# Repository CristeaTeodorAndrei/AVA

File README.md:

# AVA

AVA - Flight Computer

AVA is the rocket's main flight computer.

This is the second iteration of the flight computer

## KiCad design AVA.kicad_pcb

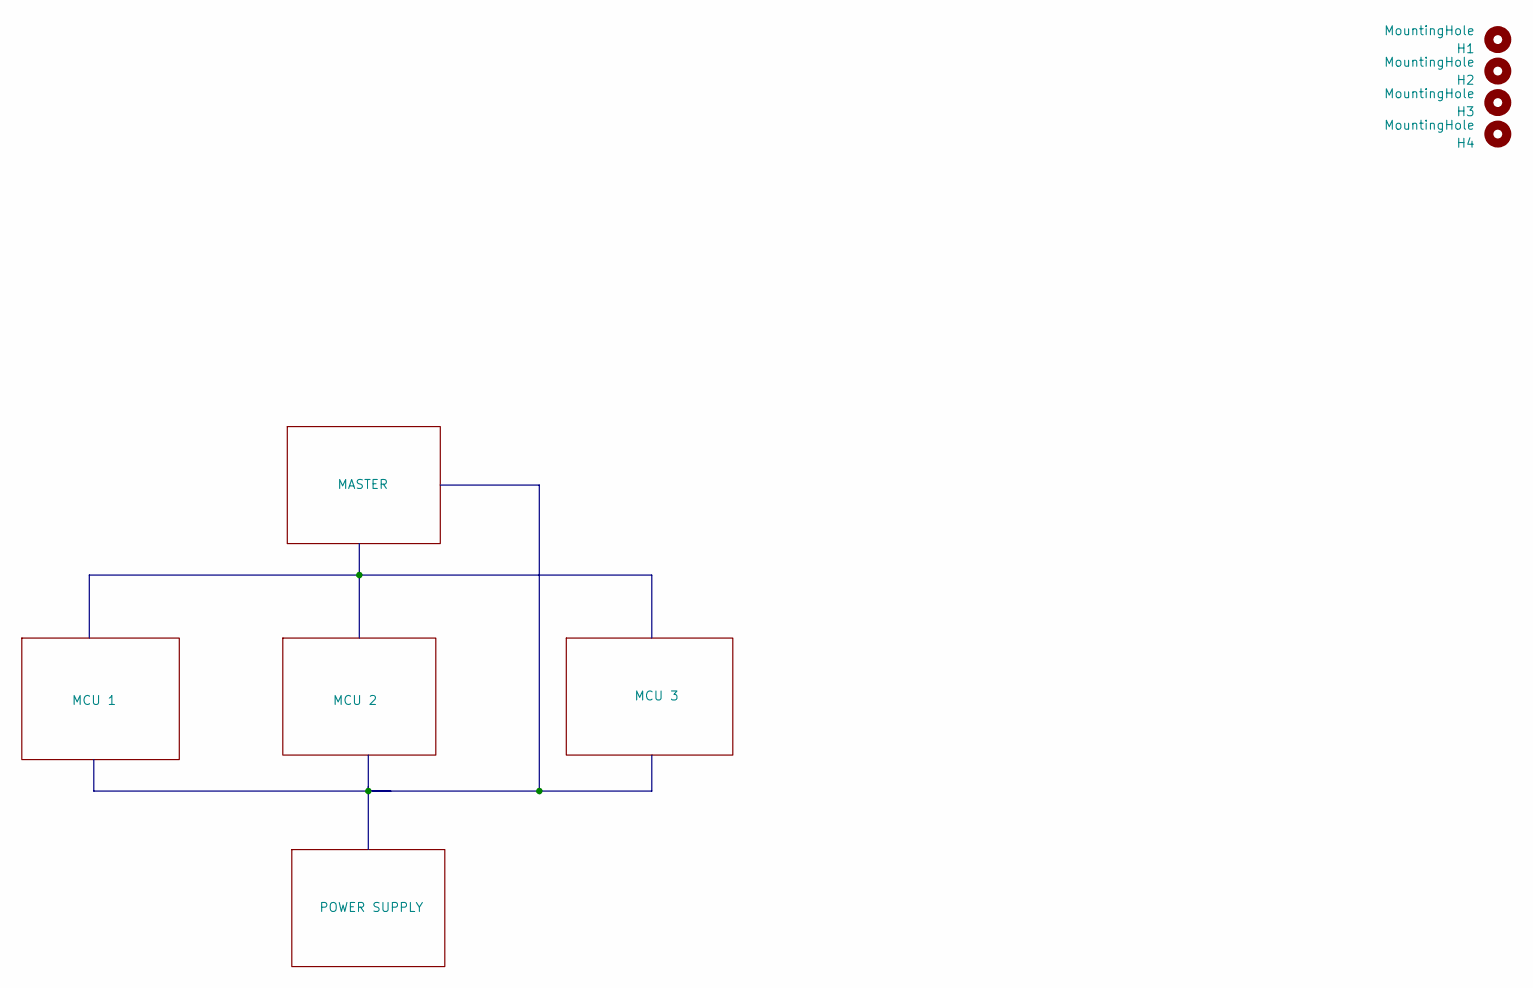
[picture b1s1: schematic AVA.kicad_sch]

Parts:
H1, H2, H3, H4: MountingHole; MountingHole_3.5mm

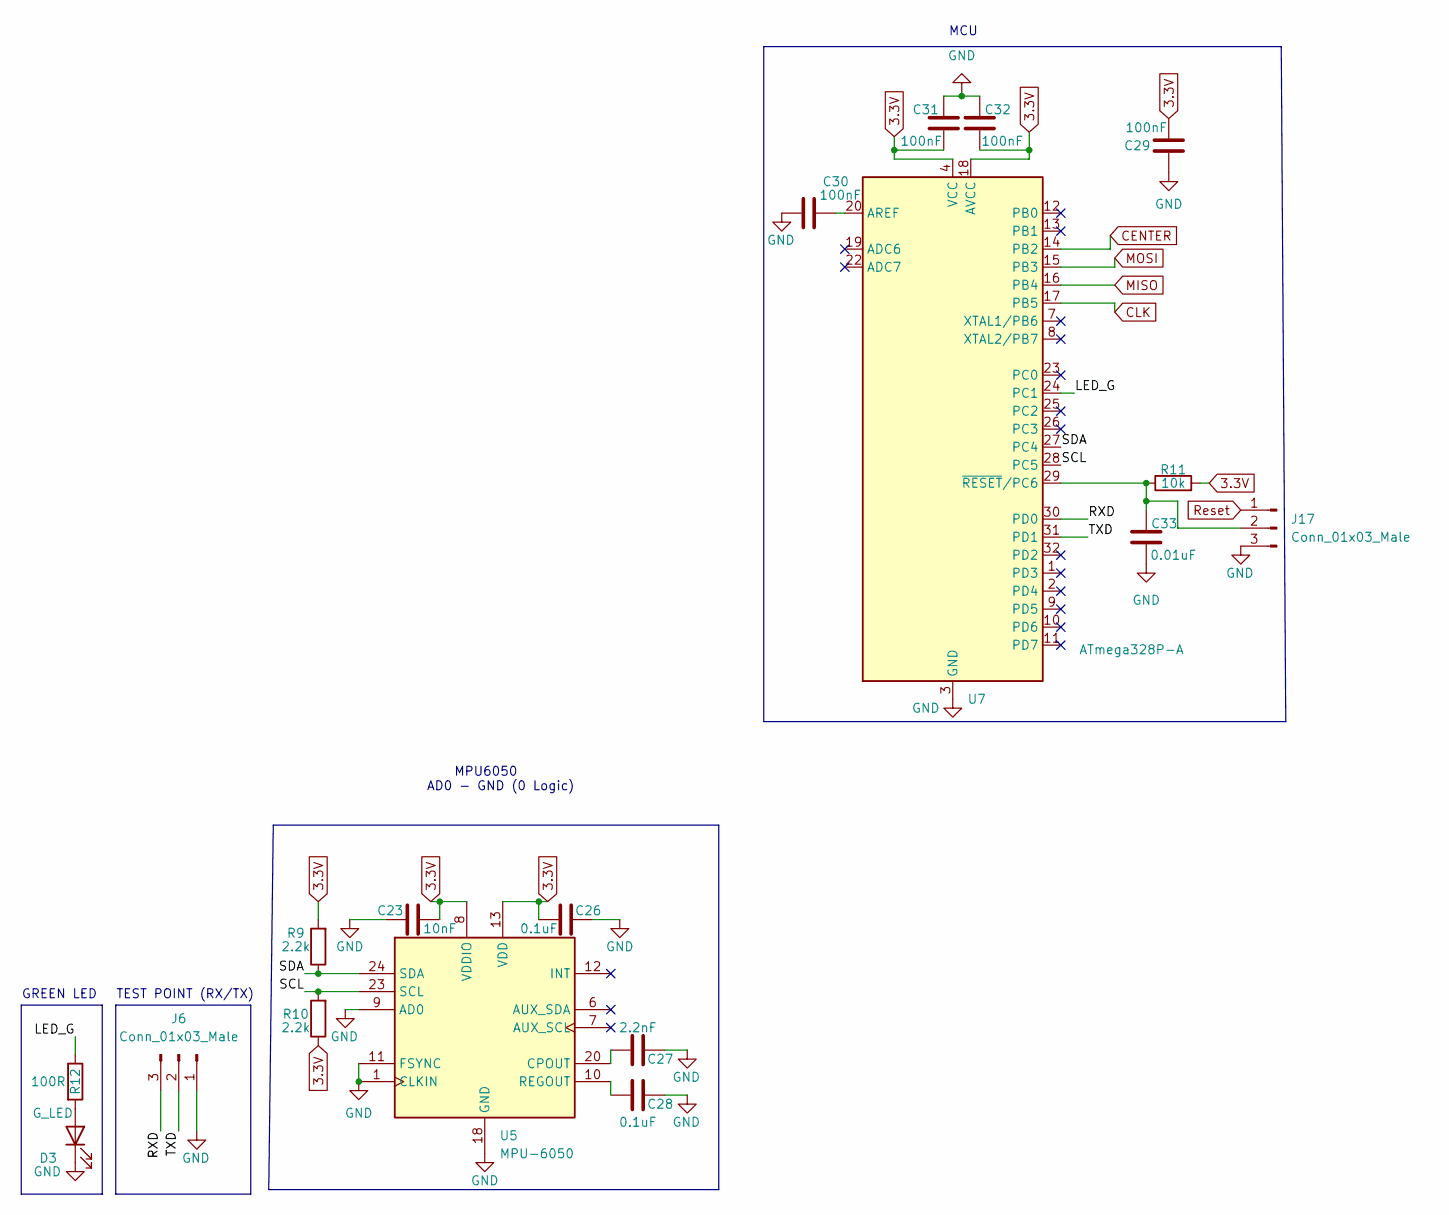
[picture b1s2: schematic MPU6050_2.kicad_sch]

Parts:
C23: 10nF; C_0603_1608Metric
C26, C28: 0.1uF; C_0603_1608Metric
C27: 2.2nF; C_0603_1608Metric
C29, C30, C31, C32: 100nF; C_0603_1608Metric
C33: 0.01uF; C_0603_1608Metric
D3: G_LED; LED_0603_1608Metric
J6, J17: Conn_01x03_Male; PinHeader_1x03_P2.54mm_Vertical
R9, R10: 2.2k; R_0603_1608Metric
R11: 10k; R_0603_1608Metric
R12: 100R; R_0603_1608Metric
U5: MPU-6050; InvenSense_QFN-24_4x4mm_P0.5mm
U7: ATmega328P-A; TQFP-32_7x7mm_P0.8mm

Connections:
3.3V: C23.2, C26.1, C29.1, C31.1, C32.1, R9.2, R10.1, R11.2, U5.8 (VDDIO), U5.13 (VDD), U7.4 (VCC), U7.6 (VCC), U7.18 (AVCC); also elsewhere on the board
/MCU 2/LED_G: R12.1, U7.24 (PC1)
/MCU 2/RXD: J6.3, U7.30 (PD0)
/MCU 2/SCL: R10.2, U5.23 (SCL), U7.28 (PC5)
/MCU 2/SDA: R9.1, U5.24 (SDA), U7.27 (PC4)
/MCU 2/TXD: J6.2, U7.31 (PD1)
CENTER: U7.14 (PB2); also elsewhere on the board
CLK: U7.17 (PB5); also elsewhere on the board
GND: C23.1, C26.2, C27.2, C28.2, C29.2, C30.1, C31.2, C32.2, C33.2, D3.1 (K), J6.1, J17.3, U5.1 (CLKIN), U5.9 (AD0), U5.11 (FSYNC), U5.18 (GND), U7.3 (GND), U7.5 (GND), U7.21 (GND); also elsewhere on the board
MISO: U7.16 (PB4); also elsewhere on the board
MOSI: U7.15 (PB3); also elsewhere on the board
unnamed: C27.1, U5.20 (CPOUT)
unnamed: C28.1, U5.10 (REGOUT)
unnamed: C30.2, U7.20 (AREF)
unnamed: C33.1, J17.2, R11.1, U7.29 (~RESET/PC6)
unnamed: D3.2 (A), R12.2
Reset: J17.1; also elsewhere on the board

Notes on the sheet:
MPU6050 AD0 - GND (0 Logic)
MCU
TEST POINT (RX/TX)
GREEN LED

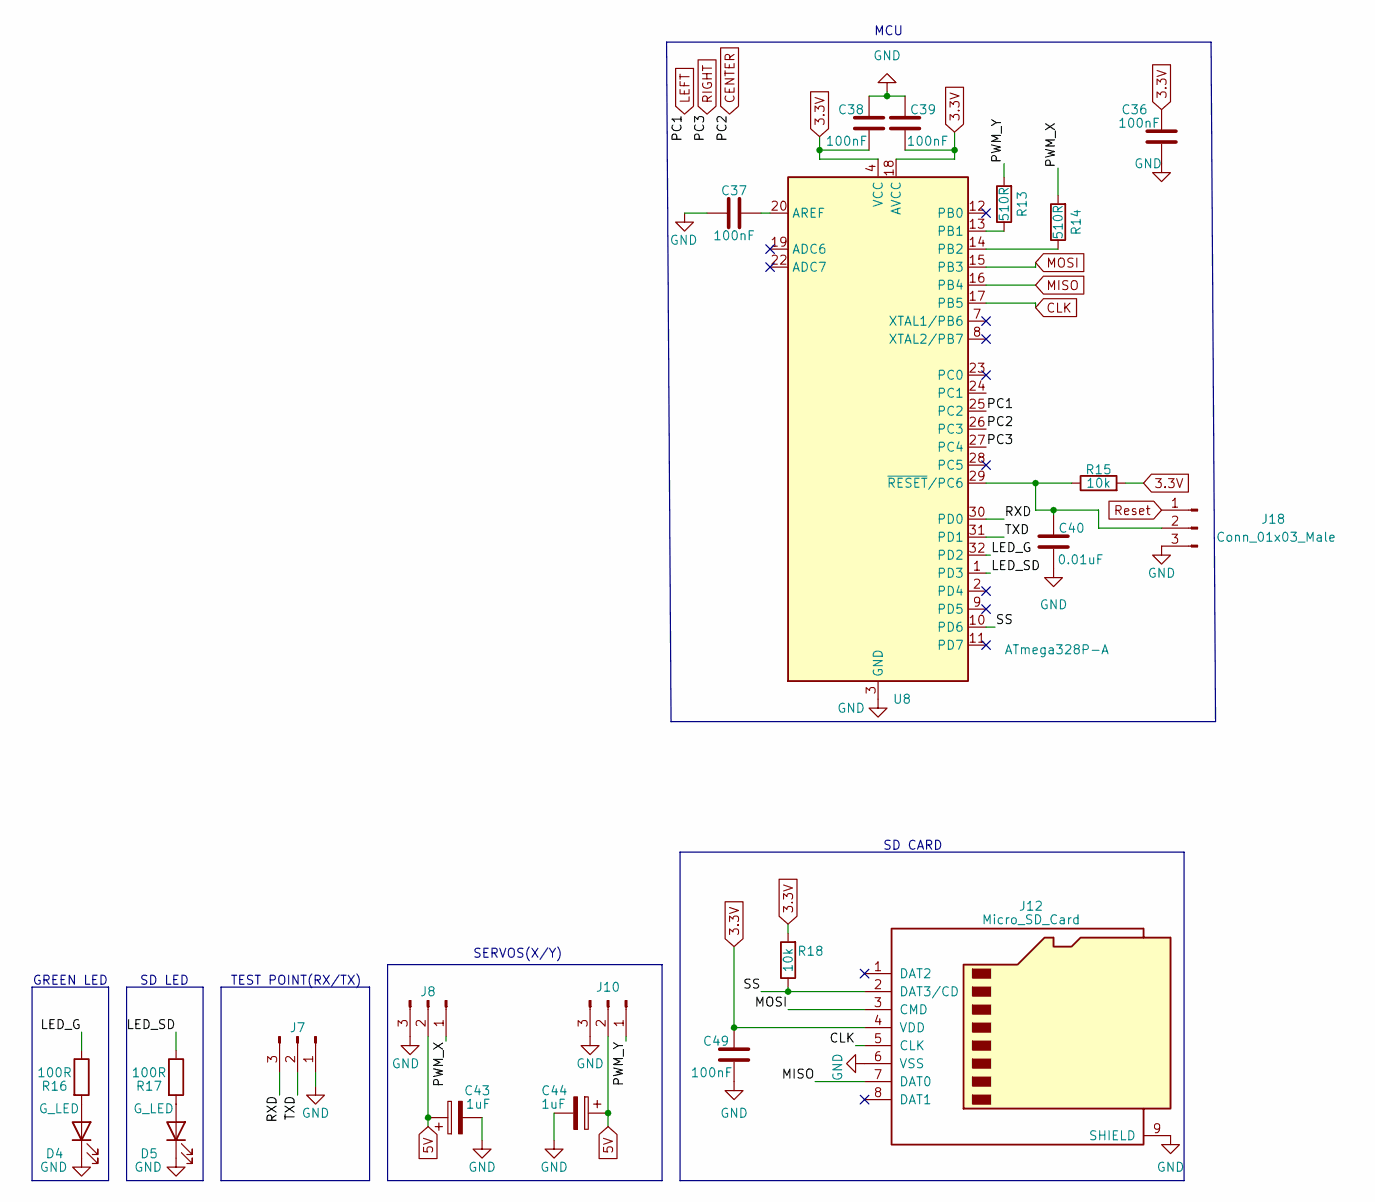
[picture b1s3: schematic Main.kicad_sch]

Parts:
C36, C37, C38, C39, C49: 100nF; C_0603_1608Metric
C40: 0.01uF; C_0603_1608Metric
C43, C44: 1uF; CP_Elec_4x5.4
D4, D5: G_LED; LED_0603_1608Metric
J7, J18: Conn_01x03_Male; PinHeader_1x03_P2.54mm_Vertical
J8: X; PinHeader_1x03_P2.54mm_Vertical
J10: Y; PinHeader_1x03_P2.54mm_Vertical
J12: Micro_SD_Card; microSD_HC_Wuerth_693072010801
R13, R14: 510R; R_0603_1608Metric
R15, R18: 10k; R_0603_1608Metric
R16, R17: 100R; R_0603_1608Metric
U8: ATmega328P-A; TQFP-32_7x7mm_P0.8mm

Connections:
3.3V: C36.1, C38.1, C39.1, C49.2, J12.4 (VDD), R15.2, R18.2, U8.4 (VCC), U8.6 (VCC), U8.18 (AVCC); also elsewhere on the board
5V: C43.1, C44.1, J8.2, J10.2; also elsewhere on the board
/MASTER/LED_G: R16.1, U8.32 (PD2)
/MASTER/LED_SD: R17.1, U8.1 (PD3)
/MASTER/PWM_X: J8.1, R14.2
/MASTER/PWM_Y: J10.1, R13.2
/MASTER/RXD: J7.3, U8.30 (PD0)
/MASTER/SS: J12.2 (DAT3/CD), R18.1, U8.10 (PD6)
/MASTER/TXD: J7.2, U8.31 (PD1)
CENTER: U8.26 (PC3); also elsewhere on the board
CLK: J12.5 (CLK), U8.17 (PB5); also elsewhere on the board
GND: C36.2, C37.1, C38.2, C39.2, C40.2, C43.2, C44.2, C49.1, D4.1 (K), D5.1 (K), J7.1, J8.3, J10.3, J12.6 (VSS), J12.9 (SHIELD), J18.3, U8.3 (GND), U8.5 (GND), U8.21 (GND); also elsewhere on the board
LEFT: U8.25 (PC2); also elsewhere on the board
MISO: J12.7 (DAT0), U8.16 (PB4); also elsewhere on the board
MOSI: J12.3 (CMD), U8.15 (PB3); also elsewhere on the board
unnamed: C37.2, U8.20 (AREF)
unnamed: C40.1, J18.2, R15.1, U8.29 (~RESET/PC6)
unnamed: D4.2 (A), R16.2
unnamed: D5.2 (A), R17.2
unnamed: R13.1, U8.13 (PB1)
unnamed: R14.1, U8.14 (PB2)
RIGHT: U8.27 (PC4); also elsewhere on the board
Reset: J18.1; also elsewhere on the board

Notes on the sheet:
SERVOS(X/Y)
SD LED
MCU
SD CARD
TEST POINT(RX/TX)
GREEN LED

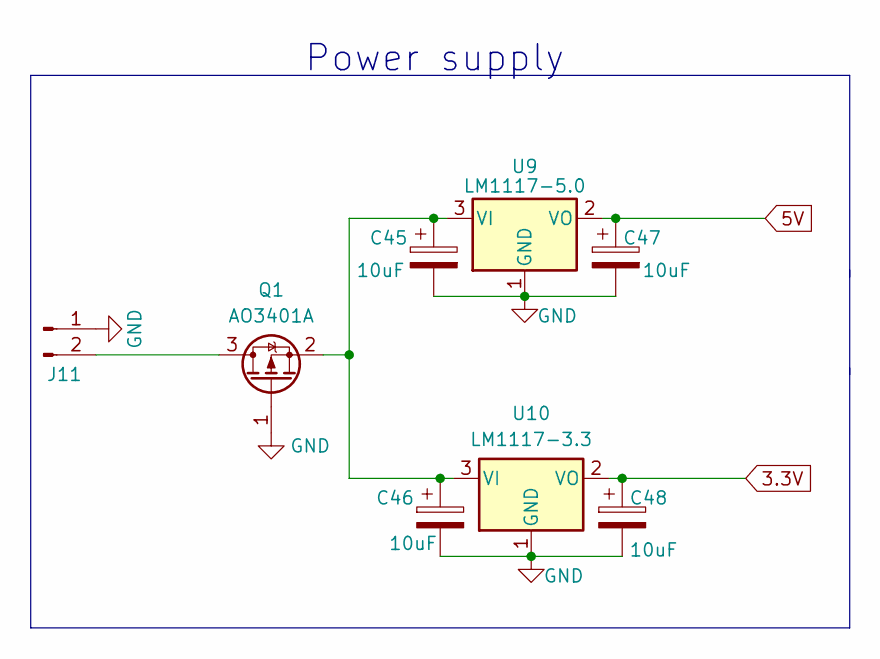
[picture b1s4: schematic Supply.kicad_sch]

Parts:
C45, C46, C47, C48: 10uF; C_1206_3216Metric
J11: Conn_01x02_Male; PinHeader_1x02_P2.54mm_Vertical
Q1: AO3401A; SOT-23
U9: LM1117-5.0; SOT-223-3_TabPin2
U10: LM1117-3.3; SOT-223-3_TabPin2

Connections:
3.3V: C48.1, U10.2 (VO); also elsewhere on the board
5V: C47.1, U9.2 (VO); also elsewhere on the board
GND: C45.2, C46.2, C47.2, C48.2, J11.1, Q1.1 (G), U9.1 (GND), U10.1 (GND); also elsewhere on the board
unnamed: C45.1, C46.1, Q1.2 (S), U9.3 (VI), U10.3 (VI)
unnamed: J11.2, Q1.3 (D)

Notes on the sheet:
Power supply

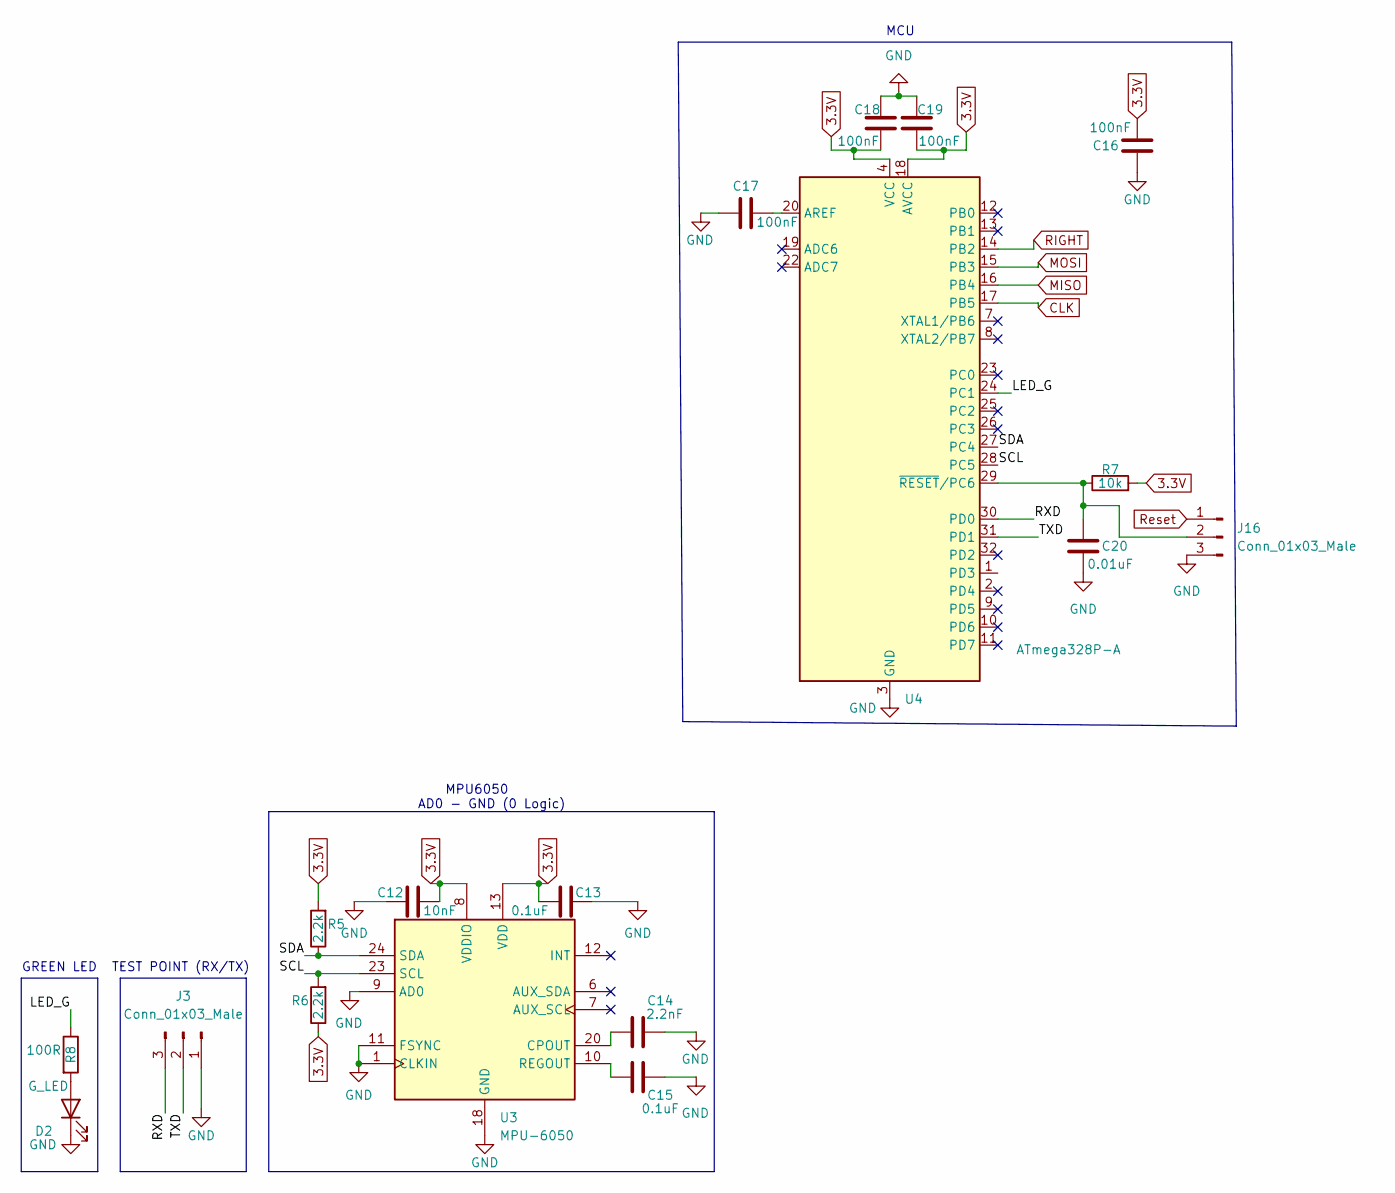
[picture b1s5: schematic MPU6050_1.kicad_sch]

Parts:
C12: 10nF; C_0603_1608Metric
C13, C15: 0.1uF; C_0603_1608Metric
C14: 2.2nF; C_0603_1608Metric
C16, C17, C18, C19: 100nF; C_0603_1608Metric
C20: 0.01uF; C_0603_1608Metric
D2: G_LED; LED_0603_1608Metric
J3, J16: Conn_01x03_Male; PinHeader_1x03_P2.54mm_Vertical
R5, R6: 2.2k; R_0603_1608Metric
R7: 10k; R_0603_1608Metric
R8: 100R; R_0603_1608Metric
U3: MPU-6050; InvenSense_QFN-24_4x4mm_P0.5mm
U4: ATmega328P-A; TQFP-32_7x7mm_P0.8mm

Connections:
3.3V: C12.2, C13.1, C16.1, C18.1, C19.1, R5.2, R6.1, R7.2, U3.8 (VDDIO), U3.13 (VDD), U4.4 (VCC), U4.6 (VCC), U4.18 (AVCC); also elsewhere on the board
/MCU 3/LED_G: R8.1, U4.24 (PC1)
/MCU 3/RXD: J3.3, U4.30 (PD0)
/MCU 3/SCL: R6.2, U3.23 (SCL), U4.28 (PC5)
/MCU 3/SDA: R5.1, U3.24 (SDA), U4.27 (PC4)
/MCU 3/TXD: J3.2, U4.31 (PD1)
CLK: U4.17 (PB5); also elsewhere on the board
GND: C12.1, C13.2, C14.2, C15.2, C16.2, C17.1, C18.2, C19.2, C20.2, D2.1 (K), J3.1, J16.3, U3.1 (CLKIN), U3.9 (AD0), U3.11 (FSYNC), U3.18 (GND), U4.3 (GND), U4.5 (GND), U4.21 (GND); also elsewhere on the board
MISO: U4.16 (PB4); also elsewhere on the board
MOSI: U4.15 (PB3); also elsewhere on the board
unnamed: C14.1, U3.20 (CPOUT)
unnamed: C15.1, U3.10 (REGOUT)
unnamed: C17.2, U4.20 (AREF)
unnamed: C20.1, J16.2, R7.1, U4.29 (~RESET/PC6)
unnamed: D2.2 (A), R8.2
RIGHT: U4.14 (PB2); also elsewhere on the board
Reset: J16.1; also elsewhere on the board

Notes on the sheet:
MPU6050 AD0 - GND (0 Logic)
MCU
GREEN LED
TEST POINT (RX/TX)

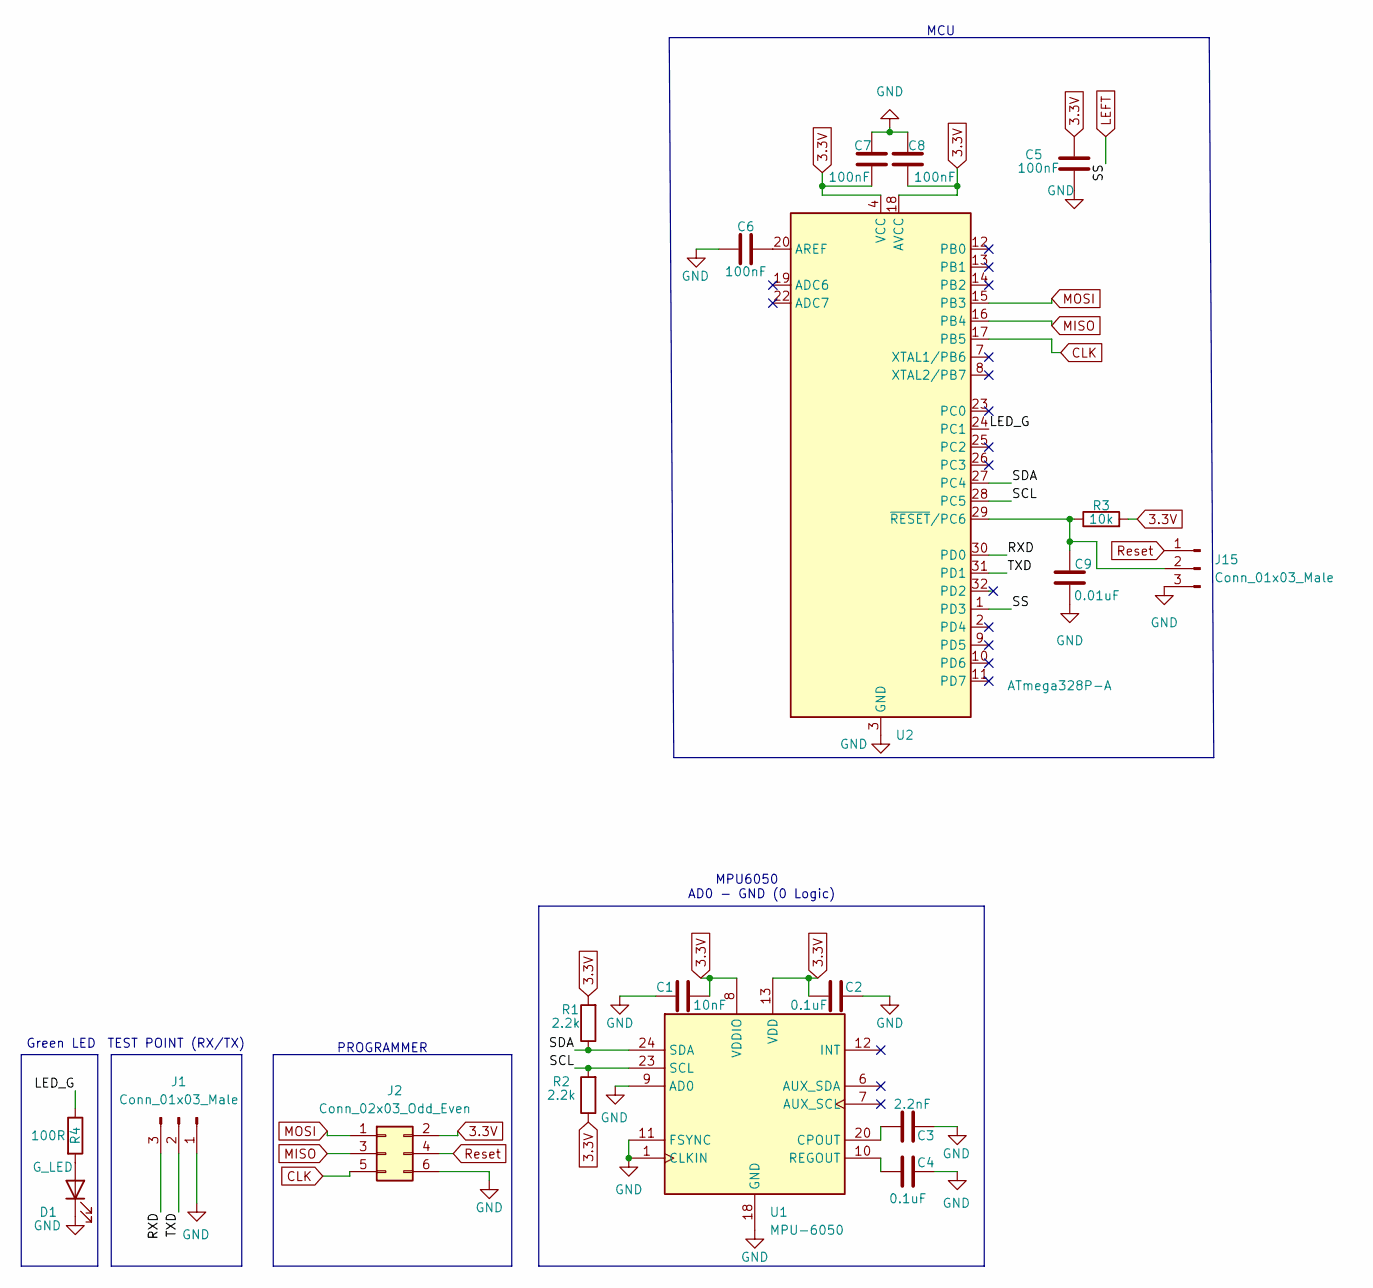
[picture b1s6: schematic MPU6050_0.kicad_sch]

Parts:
C1: 10nF; C_0603_1608Metric
C2, C4: 0.1uF; C_0603_1608Metric
C3: 2.2nF; C_0603_1608Metric
C5, C6, C7, C8: 100nF; C_0603_1608Metric
C9: 0.01uF; C_0603_1608Metric
D1: G_LED; LED_0603_1608Metric
J1, J15: Conn_01x03_Male; PinHeader_1x03_P2.54mm_Vertical
J2: Conn_02x03_Odd_Even; PinHeader_2x03_P2.54mm_Vertical
R1, R2: 2.2k; R_0603_1608Metric
R3: 10k; R_0603_1608Metric
R4: 100R; R_0603_1608Metric
U1: MPU-6050; InvenSense_QFN-24_4x4mm_P0.5mm
U2: ATmega328P-A; TQFP-32_7x7mm_P0.8mm

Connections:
3.3V: C1.2, C2.1, C5.1, C7.1, C8.1, J2.2, R1.2, R2.1, R3.2, U1.8 (VDDIO), U1.13 (VDD), U2.4 (VCC), U2.6 (VCC), U2.18 (AVCC); also elsewhere on the board
/MCU 1/LED_G: R4.1, U2.24 (PC1)
/MCU 1/RXD: J1.3, U2.30 (PD0)
/MCU 1/SCL: R2.2, U1.23 (SCL), U2.28 (PC5)
/MCU 1/SDA: R1.1, U1.24 (SDA), U2.27 (PC4)
/MCU 1/TXD: J1.2, U2.31 (PD1)
CLK: J2.5, U2.17 (PB5); also elsewhere on the board
GND: C1.1, C2.2, C3.2, C4.2, C5.2, C6.1, C7.2, C8.2, C9.2, D1.1 (K), J1.1, J2.6, J15.3, U1.1 (CLKIN), U1.9 (AD0), U1.11 (FSYNC), U1.18 (GND), U2.3 (GND), U2.5 (GND), U2.21 (GND); also elsewhere on the board
LEFT: U2.1 (PD3); also elsewhere on the board
MISO: J2.3, U2.16 (PB4); also elsewhere on the board
MOSI: J2.1, U2.15 (PB3); also elsewhere on the board
unnamed: C3.1, U1.20 (CPOUT)
unnamed: C4.1, U1.10 (REGOUT)
unnamed: C6.2, U2.20 (AREF)
unnamed: C9.1, J15.2, R3.1, U2.29 (~RESET/PC6)
unnamed: D1.2 (A), R4.2
Reset: J2.4, J15.1; also elsewhere on the board

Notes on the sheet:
MPU6050 AD0 - GND (0 Logic)
MCU
TEST POINT (RX/TX)
PROGRAMMER
Green LED

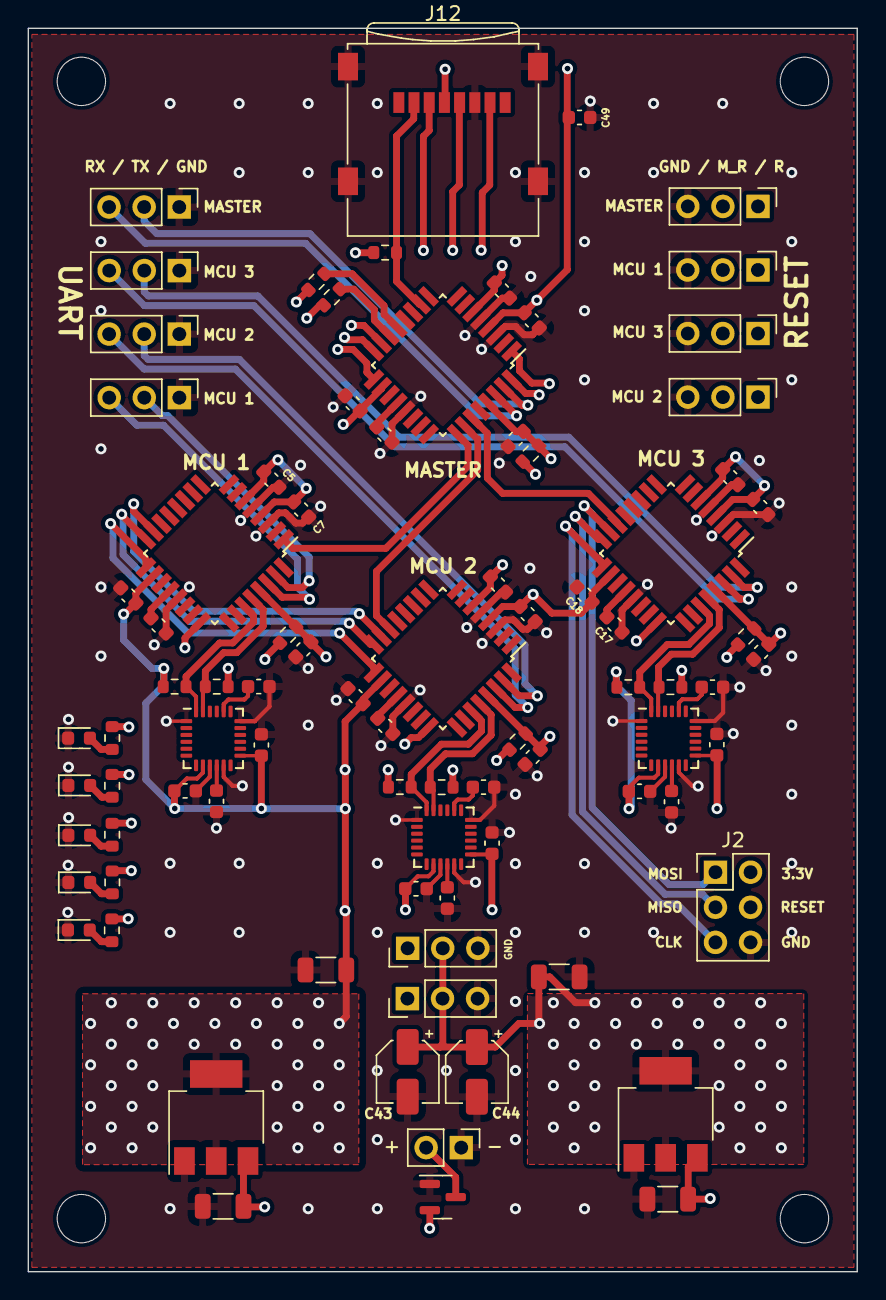
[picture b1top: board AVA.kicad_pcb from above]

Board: 4 copper layers, 60.0 x 90.0 mm, 89 parts (0 on the bottom side), 55 nets.

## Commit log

2022-11-28 Added AVA project
2022-11-28 Modified README file
2023-02-08 Added AVA project (final version)
